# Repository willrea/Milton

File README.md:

# Milton

LPC1768-based platform for high altitude balloons.

###Hardware

Includes:
* ublox MAX7 GPS
* Bosch BME280 Pressure/Humidity/Temperature Sensor
* Si4464 RF IC to transmit position via APRS
* Capability to trigger 2 Canon cameras loaded with CHDK
* MMA8452Q Accelerometer
* Supports a thermocouple for exterior temperature reading via a OneWire MAX31850

###Software###

*Overview of software functions*
* Beacon position and temps over APRS in a configurable amount of time
 * Add support for SI4464 RF IC
* Log raw NMEA strings to file on SD card
* Log sensor info with date/time and gps position on SD card, maybe in same file as NMEA strings? Would have to be 
compatible with GPSBabel or similar program.
* Trigger up to 2 cameras on set intervals
* Detect apogee via accelerometer triggering interrupt. Then trigger cameras and log gps at time of apogee

Hardware is licensed under a <a rel="license" href="http://creativecommons.org/licenses/by-sa/4.0/">Creative Commons Attribution-ShareAlike 4.0 International License</a>.

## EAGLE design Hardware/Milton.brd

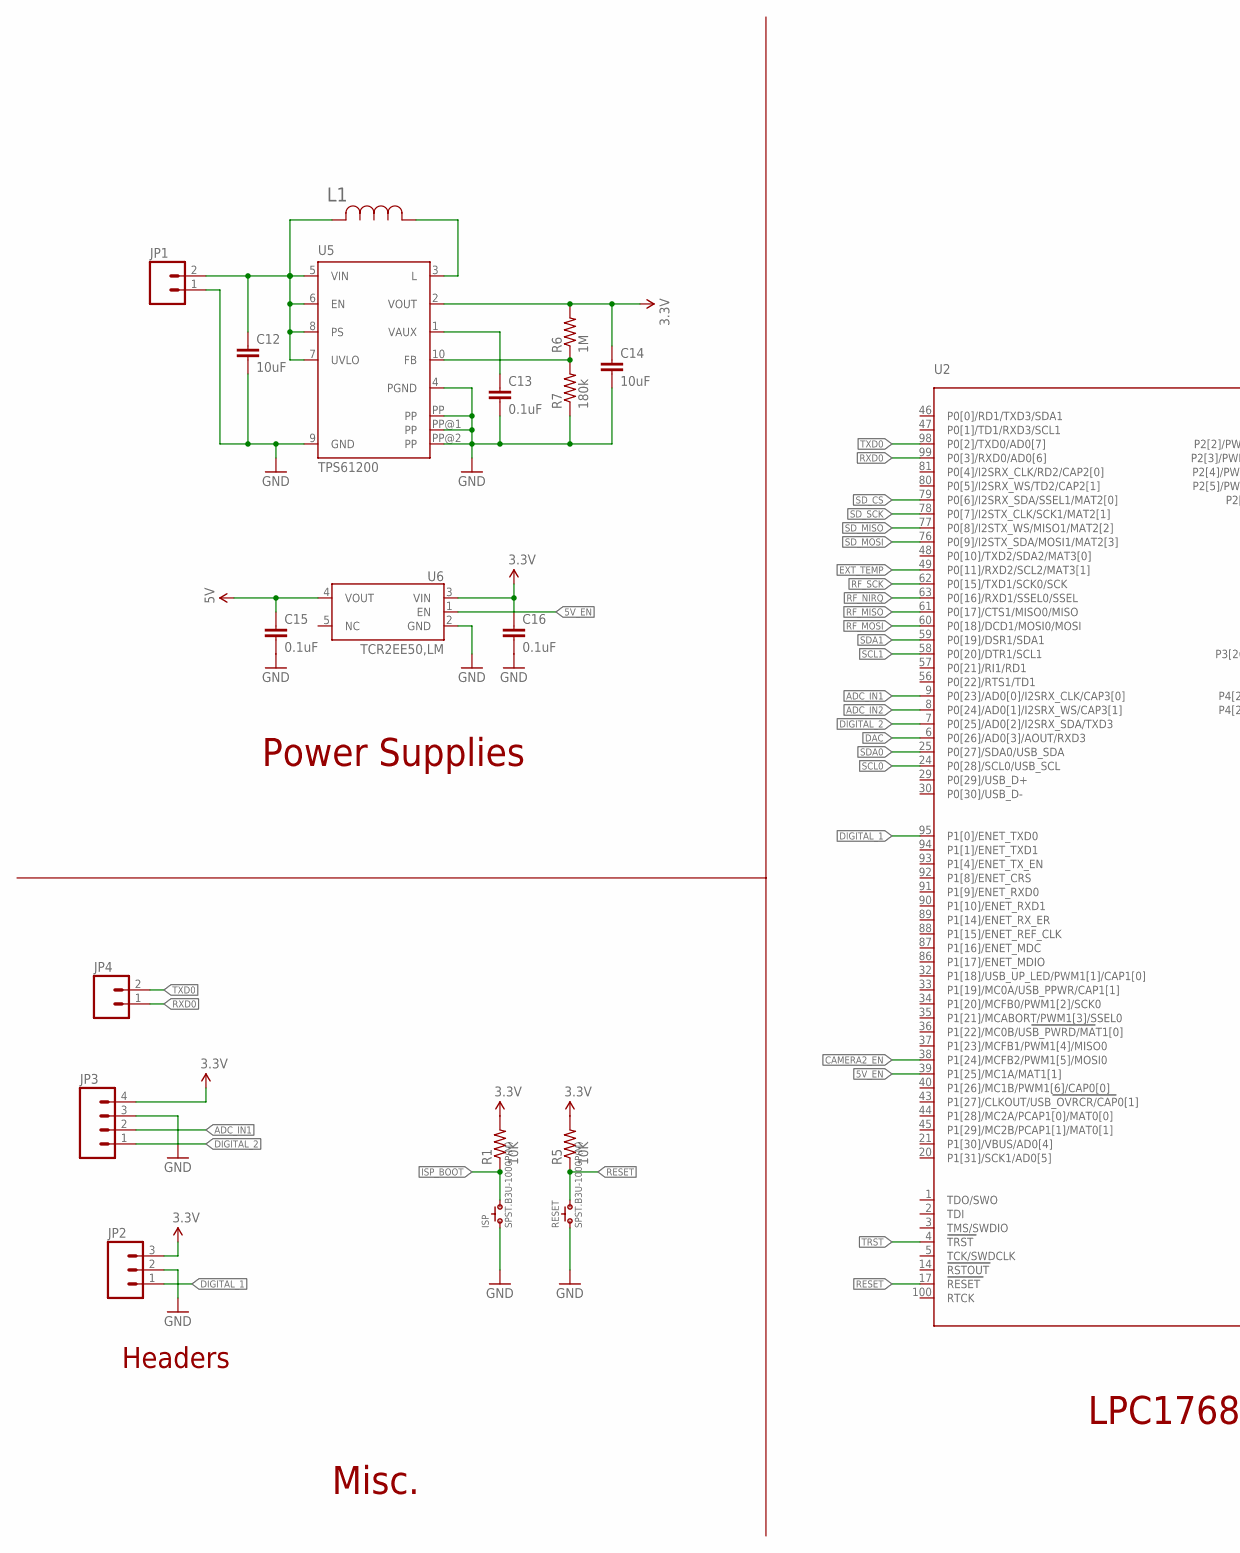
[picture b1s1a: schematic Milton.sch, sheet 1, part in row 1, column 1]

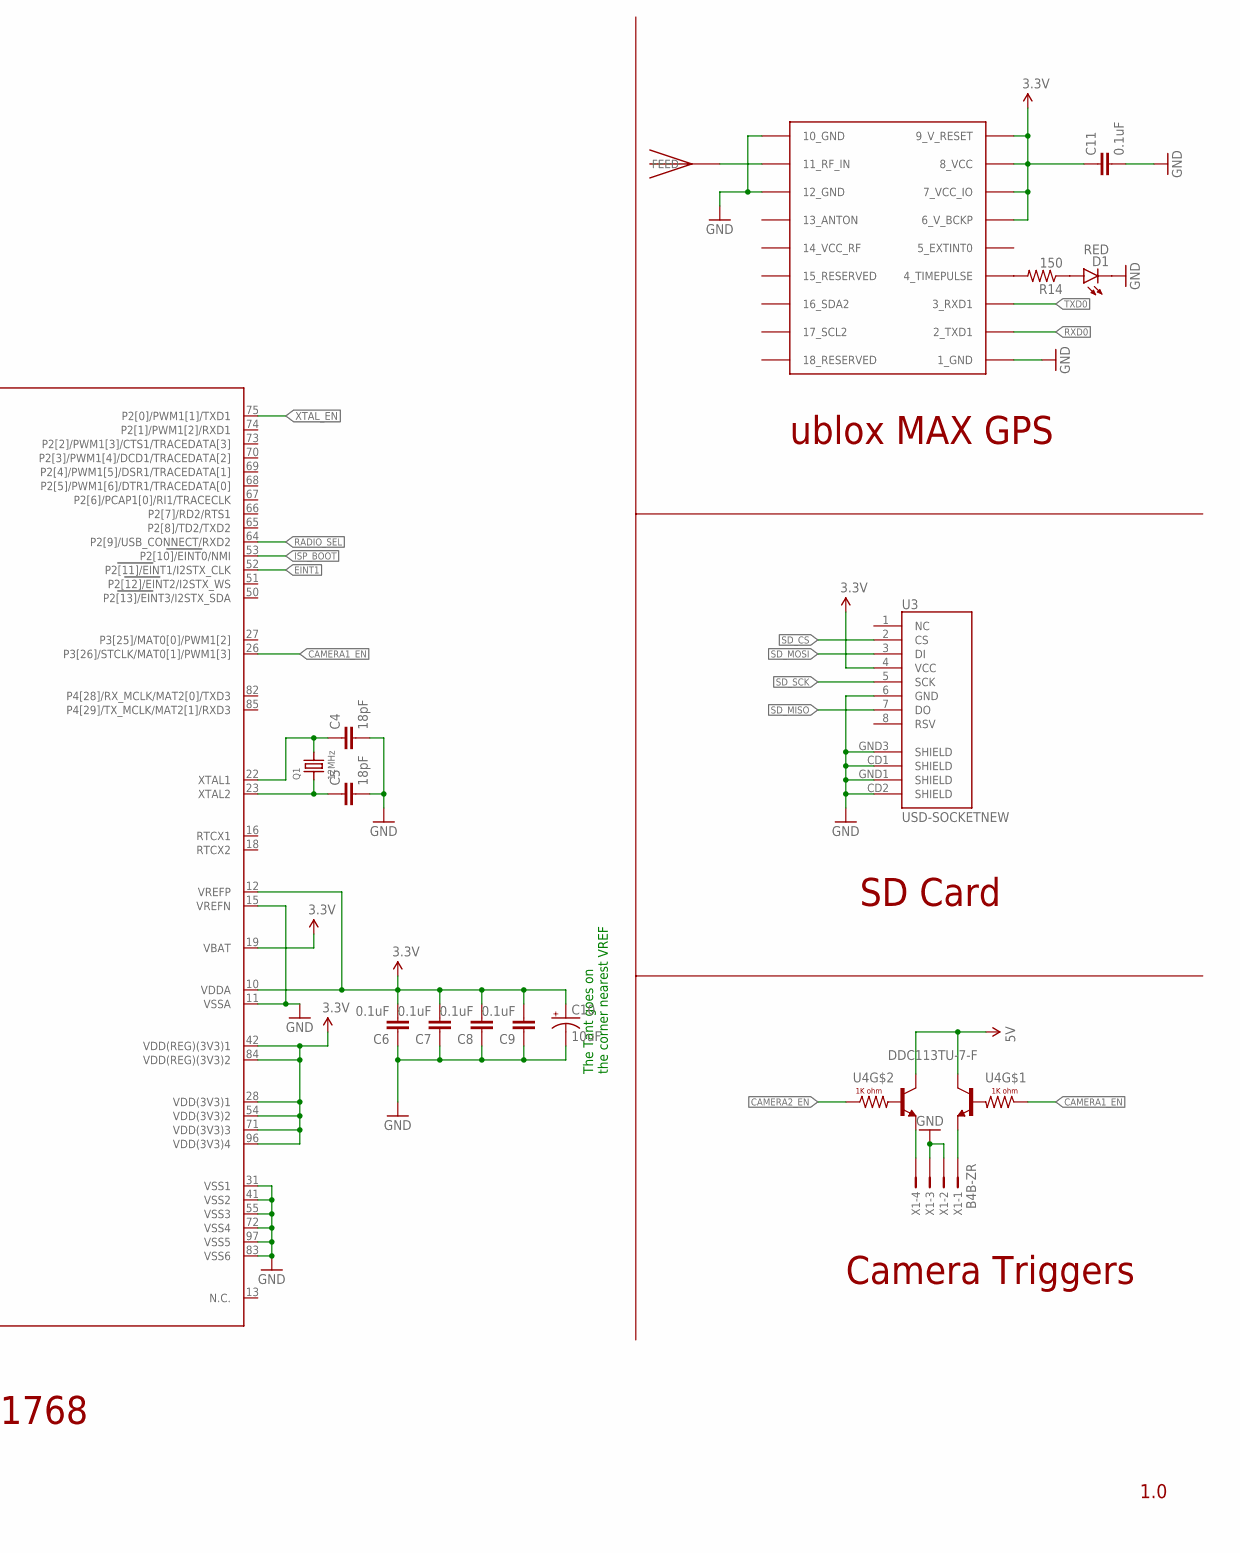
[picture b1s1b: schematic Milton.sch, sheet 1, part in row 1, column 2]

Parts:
C4, C5: 18pF; 0805; MPN C0603C180K3GACTU
C6, C7, C8, C9, C11, C13, C15, C16: 0.1uF; 0603-CAP; MPN CL10B104KO8NNNC
C10: 10uF; EIA3216; MPN F931A106KAA
C12, C14: 10uF; 0805; MPN GRM21BR61C106KE15L
D1: RED; LED-0603; MPN LS L29K-G1J2-1-Z
ISP: SPST.B3U-1000P(M); B3U-1000P(M)
JP1: M02JST-PTH-2; JST-2-PTH; MPN S2B-PH-K-S(LF)(SN)
JP2: M03PTH; 1X03
JP3: M04PTH; 1X04
JP4: M02LOCK; 1X02_LOCK
L1: SRN3015-2R2M; IND_BOURNS_SRN3015; MPN SRN3015-4R7M
Q1: 12MHz; CRYSTAL_3.2X2.5; MPN 7V-12.000MAHE-T
R1, R5: 10K; 0603-RES; MPN ESR03EZPJ103
R6: 1M; 0603-RES; MPN MCT06030C1004FP500
R7: 180k; 0603-RES; MPN RC1608F184CS
R14: 150; 0603-RES; MPN ESR03EZPJ151
RESET: SPST.B3U-1000P(M); B3U-1000P(M)
U2: LPC1768; LQFP100; MPN LPC1768FBD100,551
U3: USD-SOCKETNEW; MICRO-SD-SOCKET-PP; MPN 101-00660-68-6
U4: DDC113TU-7-F; SC70−6; MPN DDC113TU-7-F
U5: TPS61200; S-PDSO-N10; MPN TPS61200DRCR
U6: TCR2EE50,LM; SOT50P160X60-5N
U$2: 1575AT43A40; JTI_ANTENNA-1575AT43A40; MPN 1575AT43A0040E
U$3: UBLOX_MAX; MPN MAX-7C-0
X1: B4B-ZR

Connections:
3.3V: C6.2, C7.2, C8.2, C9.2, C10.A (+), C11.1, C14.1, C16.1, JP2.3, JP3.4, R1.2, R5.2, R6.2, U2.10 (VDDA), U2.12 (VREFP), U2.19 (VBAT), U2.28 (VDD(3V3)1), U2.42 (VDD(REG)(3V3)1), U2.54 (VDD(3V3)2), U2.71 (VDD(3V3)3), U2.84 (VDD(REG)(3V3)2), U2.96 (VDD(3V3)4), U3.4 (VCC), U5.2 (VOUT), U6.3 (VIN), U$3.6_V_BCKP, U$3.7_VCC_IO, U$3.8_VCC, U$3.9_V_RESET; also elsewhere on the board
5V: C15.1, U4.3 (C), U4.6 (C), U6.4 (VOUT)
5V_EN: U2.39 (P1[25]/MC1A/MAT1[1]), U6.1 (EN)
ADC_IN1: JP3.2, U2.9 (P0[23]/AD0[0]/I2SRX_CLK/CAP3[0])
ADC_IN2: U2.8 (P0[24]/AD0[1]/I2SRX_WS/CAP3[1])
CAM1: U4.1 (E), X1.1
CAM2: U4.4 (E), X1.4
CAMERA1_EN: U2.26 (P3[26]/STCLK/MAT0[1]/PWM1[3]), U4.2 (B)
CAMERA2_EN: U2.38 (P1[24]/MCFB2/PWM1[5]/MOSI0), U4.5 (B)
DAC: U2.6 (P0[26]/AD0[3]/AOUT/RXD3); also elsewhere on the board
DIGITAL_1: JP2.1, U2.95 (P1[0]/ENET_TXD0)
DIGITAL_2: JP3.1, U2.7 (P0[25]/AD0[2]/I2SRX_SDA/TXD3)
EINT1: U2.52 (P2[11]/EINT1/I2STX_CLK); also elsewhere on the board
EXT_TEMP: U2.49 (P0[11]/RXD2/SCL2/MAT3[1]); also elsewhere on the board
GND: C4.2, C5.2, C6.1, C7.1, C8.1, C9.1, C10.C (-), C11.2, C12.2, C13.2, C14.2, C15.2, C16.2, D1.C, ISP.1, JP1.1, JP2.2, JP3.3, R7.1, RESET.1, U2.11 (VSSA), U2.15 (VREFN), U2.31 (VSS1), U2.41 (VSS2), U2.55 (VSS3), U2.72 (VSS4), U2.83 (VSS6), U2.97 (VSS5), U3.6 (GND), U3.CD1 (SHIELD), U3.CD2 (SHIELD), U3.GND1 (SHIELD), U3.GND3 (SHIELD), U5.4 (PGND), U5.9 (GND), U5.PP, U5.PP@1 (PP), U5.PP@2 (PP), U6.2 (GND), U$3.1_GND, U$3.10_GND, U$3.12_GND, X1.2, X1.3; also elsewhere on the board
IC6_RTC1: C4.1, Q1.2, U2.22 (XTAL1)
IC6_RTC2: C5.1, Q1.1, U2.23 (XTAL2)
ISP_BOOT: ISP.2, R1.1, U2.53 (P2[10]/EINT0/NMI)
unnamed: R6.1, R7.2, U5.10 (FB)
unnamed: U$2.FEED, U$3.11_RF_IN
unnamed: D1.A, R14.1
unnamed: L1.1, U5.3 (L)
unnamed: R14.2, U$3.4_TIMEPULSE
RADIO_SEL: U2.64 (P2[9]/USB_CONNECT/RXD2); also elsewhere on the board
RESET: R5.1, RESET.2, U2.17 (RESET)
RF_MISO: U2.61 (P0[17]/CTS1/MISO0/MISO); also elsewhere on the board
RF_MOSI: U2.60 (P0[18]/DCD1/MOSI0/MOSI); also elsewhere on the board
RF_NIRQ: U2.63 (P0[16]/RXD1/SSEL0/SSEL); also elsewhere on the board
RF_SCK: U2.62 (P0[15]/TXD1/SCK0/SCK); also elsewhere on the board
RXD0: JP4.1, U2.99 (P0[3]/RXD0/AD0[6]), U$3.2_TXD1
SCL0: U2.24 (P0[28]/SCL0/USB_SCL); also elsewhere on the board
SCL1: U2.58 (P0[20]/DTR1/SCL1); also elsewhere on the board
SDA0: U2.25 (P0[27]/SDA0/USB_SDA); also elsewhere on the board
SDA1: U2.59 (P0[19]/DSR1/SDA1); also elsewhere on the board
SD_CS: U2.79 (P0[6]/I2SRX_SDA/SSEL1/MAT2[0]), U3.2 (CS)
SD_MISO: U2.77 (P0[8]/I2STX_WS/MISO1/MAT2[2]), U3.7 (DO)
SD_MOSI: U2.76 (P0[9]/I2STX_SDA/MOSI1/MAT2[3]), U3.3 (DI)
SD_SCK: U2.78 (P0[7]/I2STX_CLK/SCK1/MAT2[1]), U3.5 (SCK)
TRST: U2.4 (TRST)
TXD0: JP4.2, U2.98 (P0[2]/TXD0/AD0[7]), U$3.3_RXD1
VAUX: C13.1, U5.1 (VAUX)
VIN: C12.1, JP1.2, L1.2, U5.5 (VIN), U5.6 (EN), U5.7 (UVLO), U5.8 (PS)
XTAL_EN: U2.75 (P2[0]/PWM1[1]/TXD1); also elsewhere on the board

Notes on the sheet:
The Tant goes on the corner nearest VREF
LPC1768
ublox MAX GPS
SD Card
Camera Triggers
Power Supplies
1.0
Headers
Misc.

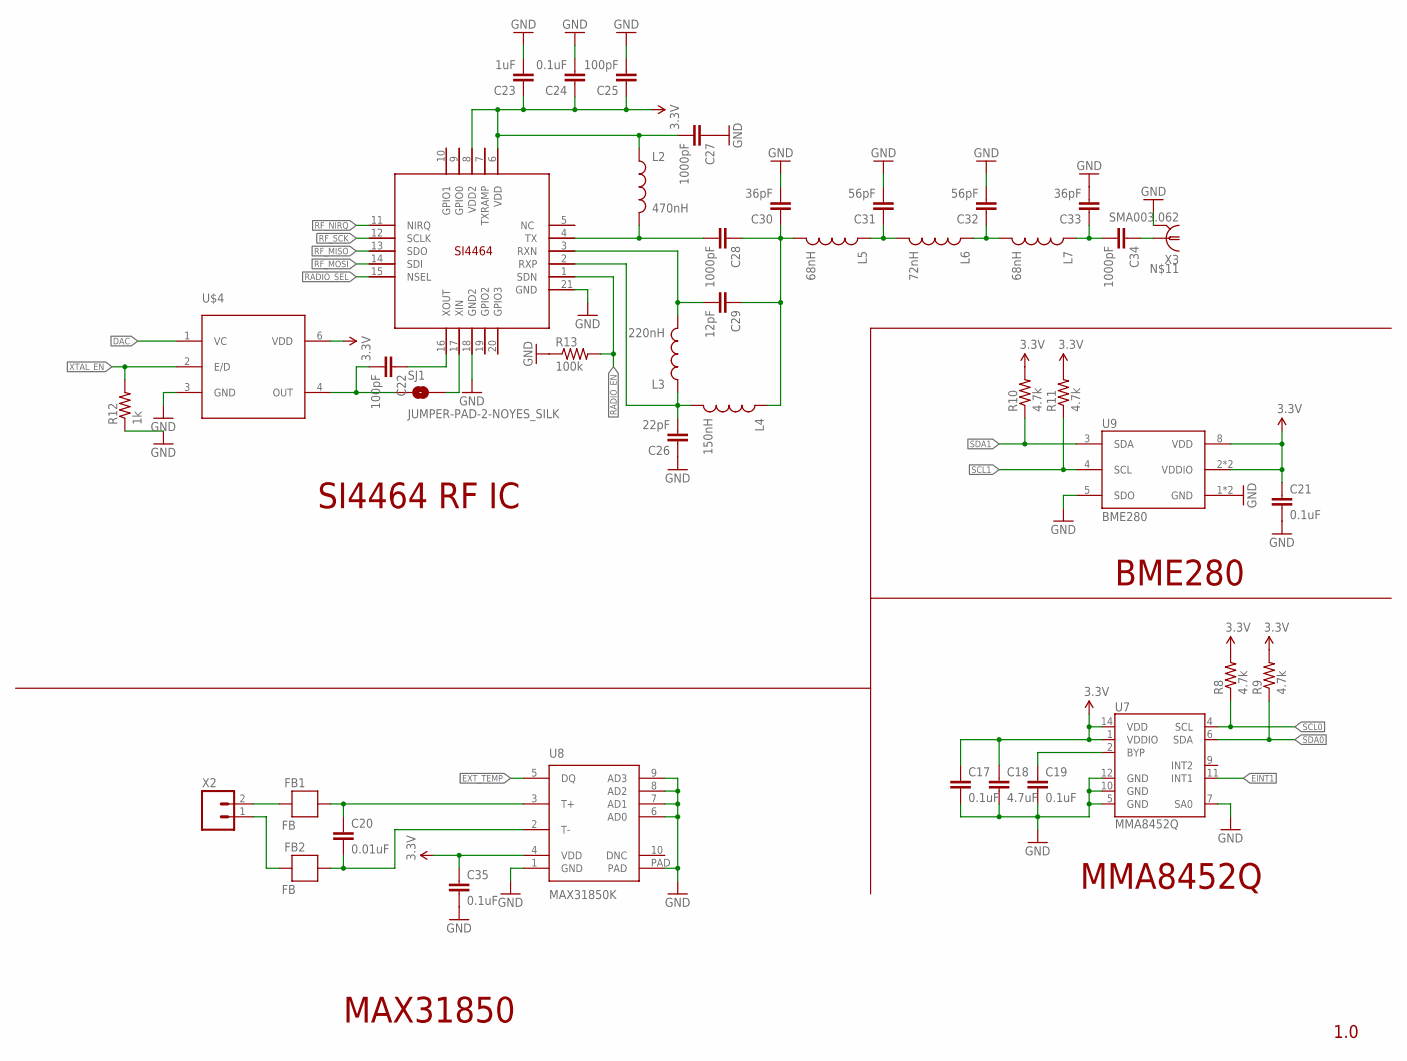
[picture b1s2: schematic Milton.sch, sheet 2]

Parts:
C17, C19, C21, C35: 0.1uF; 0805; MPN CL10B104KO8NNNC
C18: 4.7uF; 0603-CAP; MPN CC0603KRX5R6BB475
C20: 0.01uF; 0805; MPN C0603C103J5RACTU
C22, C25: 100pF; 0603-CAP; MPN CL10B101KB8NNNC
C23: 1uF; 0603-CAP; MPN CL10B105KP8NNNC
C24: 0.1uF; 0603-CAP; MPN CL10B104KO8NNNC
C26: 22pF; 0805; MPN C1608C0G1H220J080AA
C27, C28: 1000pF; 0603-CAP; MPN C0603C102J5RACTU
C29: 12pF; 0603-CAP; MPN CL10C120JB8NNNC
C30, C33: 36pF; 0603-CAP; MPN GRM1885C1H360JA01D
C31, C32: 56pF; 0603-CAP; MPN CL10C560JB8NNNC
C34: 1000pF; 0805; MPN C0603C102J5RACTU
FB1, FB2: FB; 0603; MPN BLM18PG471SN1D
L2: 470nH; 0603; MPN L0603CR47JRMST
L3: 220nH; 0603; MPN LQW18ANR22G00D
L4: 150nH; 0603; MPN LQW18ANR15G00D
L5, L7: 68nH; 0603; MPN LQW18AN68NG00D
L6: 72nH; 0603; MPN LQW18AN72NG00D
R8, R9, R10, R11: 4.7k; 0603-RES; MPN ERJ-3GEYJ472V
R12: 1k; 0603-RES; MPN RMCF0603JT1K00
R13: 100k; 0603-RES; MPN MCT06030C1003FP500
SJ1: JUMPER-PAD-2-NOYES_SILK; PAD-JUMPER-2-NO_YES_SILK
U7: MMA8452Q; QFN-16_0.5MM; MPN MMA8452QT
U8: MAX31850K; 10-TDFN-EP; MPN MAX31850TATB+
U9: BME280
U10: SI4464; QFN20+GNDPAD; MPN SI4464-B1B-FM
U$4: FVXO-HC53BR-27; 6-SMD; MPN FVXO-HC53BR-27
X2: M023.5MM; SCREWTERMINAL-3.5MM-2; MPN ED555/2DS
X3: SMA003.062

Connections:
3.3V: C17.1, C18.1, C21.1, C23.1, C24.1, C25.1, C27.2, C35.1, L2.1, R8.2, R9.2, R10.2, R11.2, U7.1 (VDDIO), U7.14 (VDD), U8.4 (VDD), U9.2 (VDDIO), U9.6 (VDDIO), U9.8 (VDD), U10.6 (VDD), U10.8 (VDD2), U$4.6 (VDD); also elsewhere on the board
DAC: U$4.1 (VC); also elsewhere on the board
EINT1: U7.11 (INT1); also elsewhere on the board
EXT_TEMP: U8.5 (DQ); also elsewhere on the board
GND: C17.2, C18.2, C19.2, C21.2, C23.2, C24.2, C25.2, C26.1, C27.1, C30.2, C31.2, C32.2, C33.2, C35.2, R12.1, R13.1, U7.5 (GND), U7.7 (SA0), U7.10 (GND), U7.12 (GND), U8.1 (GND), U8.6 (AD0), U8.7 (AD1), U8.8 (AD2), U8.9 (AD3), U8.PAD, U9.1 (GND), U9.5 (SDO), U9.7 (GND), U10.18 (GND2), U10.21 (GND), U$4.3 (GND), X3.C2 (2), X3.C3 (2), X3.C4 (2), X3.C5 (2); also elsewhere on the board
unnamed: C19.1, U7.2 (BYP)
unnamed: C22.1, U10.16 (XOUT)
unnamed: C32.1, L6.1, L7.2
unnamed: C28.2, L2.2, U10.4 (TX)
unnamed: C29.2, L3.2, U10.3 (RXN)
unnamed: C22.2, SJ1.1, U$4.4 (OUT)
unnamed: C26.2, L3.1, L4.2, U10.2 (RXP)
unnamed: C33.1, C34.2, L7.1
unnamed: C34.1, X3.RF (1)
unnamed: C28.1, C29.1, C30.1, L4.1, L5.2
unnamed: C31.1, L5.1, L6.2
unnamed: SJ1.2, U10.17 (XIN)
RADIO_EN: R13.2, U10.1 (SDN)
RADIO_SEL: U10.15 (NSEL); also elsewhere on the board
RF_MISO: U10.13 (SDO); also elsewhere on the board
RF_MOSI: U10.14 (SDI); also elsewhere on the board
RF_NIRQ: U10.11 (NIRQ); also elsewhere on the board
RF_SCK: U10.12 (SCLK); also elsewhere on the board
SCL0: R8.1, U7.4 (SCL); also elsewhere on the board
SCL1: R11.1, U9.4 (SCL); also elsewhere on the board
SDA0: R9.1, U7.6 (SDA); also elsewhere on the board
SDA1: R10.1, U9.3 (SDA); also elsewhere on the board
TM_FILT: C20.2, FB2.1, U8.2 (T-)
TM_RAW: FB2.2, X2.1
TP_FILT: C20.1, FB1.1, U8.3 (T+)
TP_RAW: FB1.2, X2.2
XTAL_EN: R12.2, U$4.2 (E/D); also elsewhere on the board

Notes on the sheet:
SI4464 RF IC
BME280
MMA8452Q
MAX31850
1.0

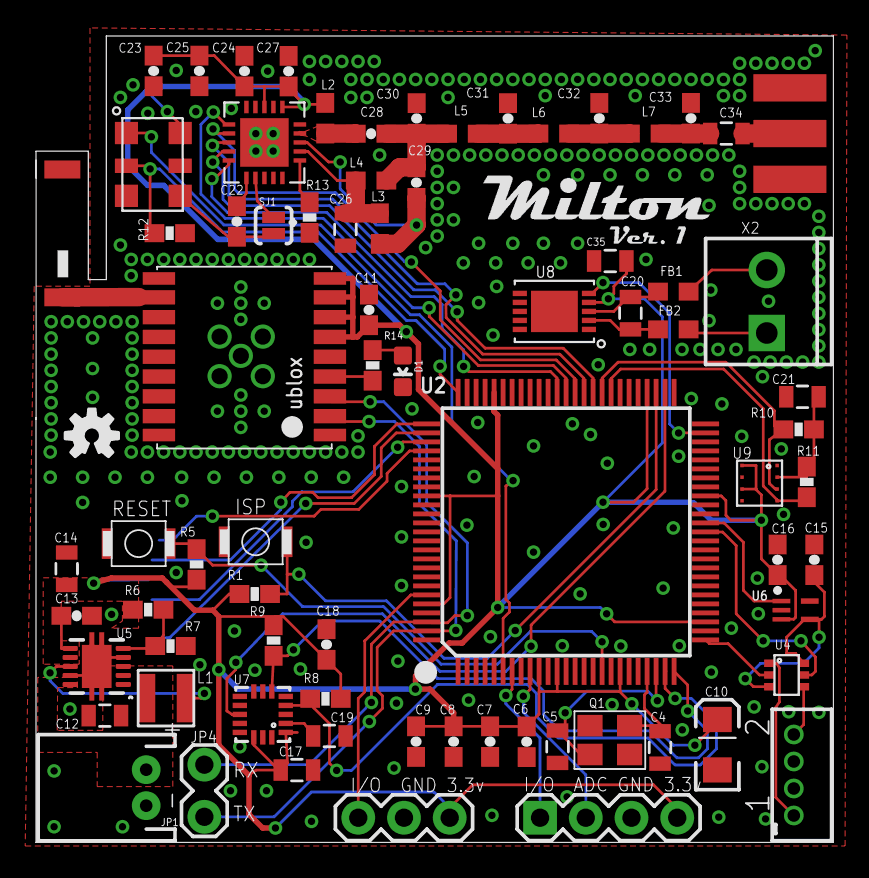
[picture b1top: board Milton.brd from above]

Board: 2 copper layers, 44.3 x 44.8 mm, 77 parts (1 on the bottom side), 58 nets.

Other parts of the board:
U$1: OSHW-LOGO-S

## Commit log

2015-03-21 :octocat: Added .gitattributes
2015-03-21 Initial commit.
2015-03-25 Cleaning
    Optimize traces, add more part numbers.
2015-03-25 Update README.md
    Add thermocouple line.
2015-03-27 Update.
    Shifted components to make room to break out another digital io
2015-03-27 Update README.md
    Add image and license info.
2015-03-31 Update
    Continue cleaning up traces and adding part numbers
2015-04-01 Cleanup
    Cleaning up layout. Optimizing traces by changing pins used.
2015-04-01 Fix
    Forgot to connect pins 10 & 12 of ublox to GND
2015-04-01 Add software section
2015-04-01 Change SMA connector
2015-04-02 Added info to README
2015-04-03 Cleanup schematics
    Cleanup schematics and added images
2015-04-03 Add LED to GPS PPS output
2015-04-09 Update
    Removed FTDI from board. Added tx/rx header and isp button
    Adjusted gps antenna position
2015-04-17 Cleanup

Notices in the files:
parts and their libraries:
SparkFun-Resistors: Licensing: CC v3.0 Share-Alike You are welcome to use this library for commercial purposes.
microbuilder: This work is placed in the public domain, and may be freely used for commercial and non-commercial work with the following conditions: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
